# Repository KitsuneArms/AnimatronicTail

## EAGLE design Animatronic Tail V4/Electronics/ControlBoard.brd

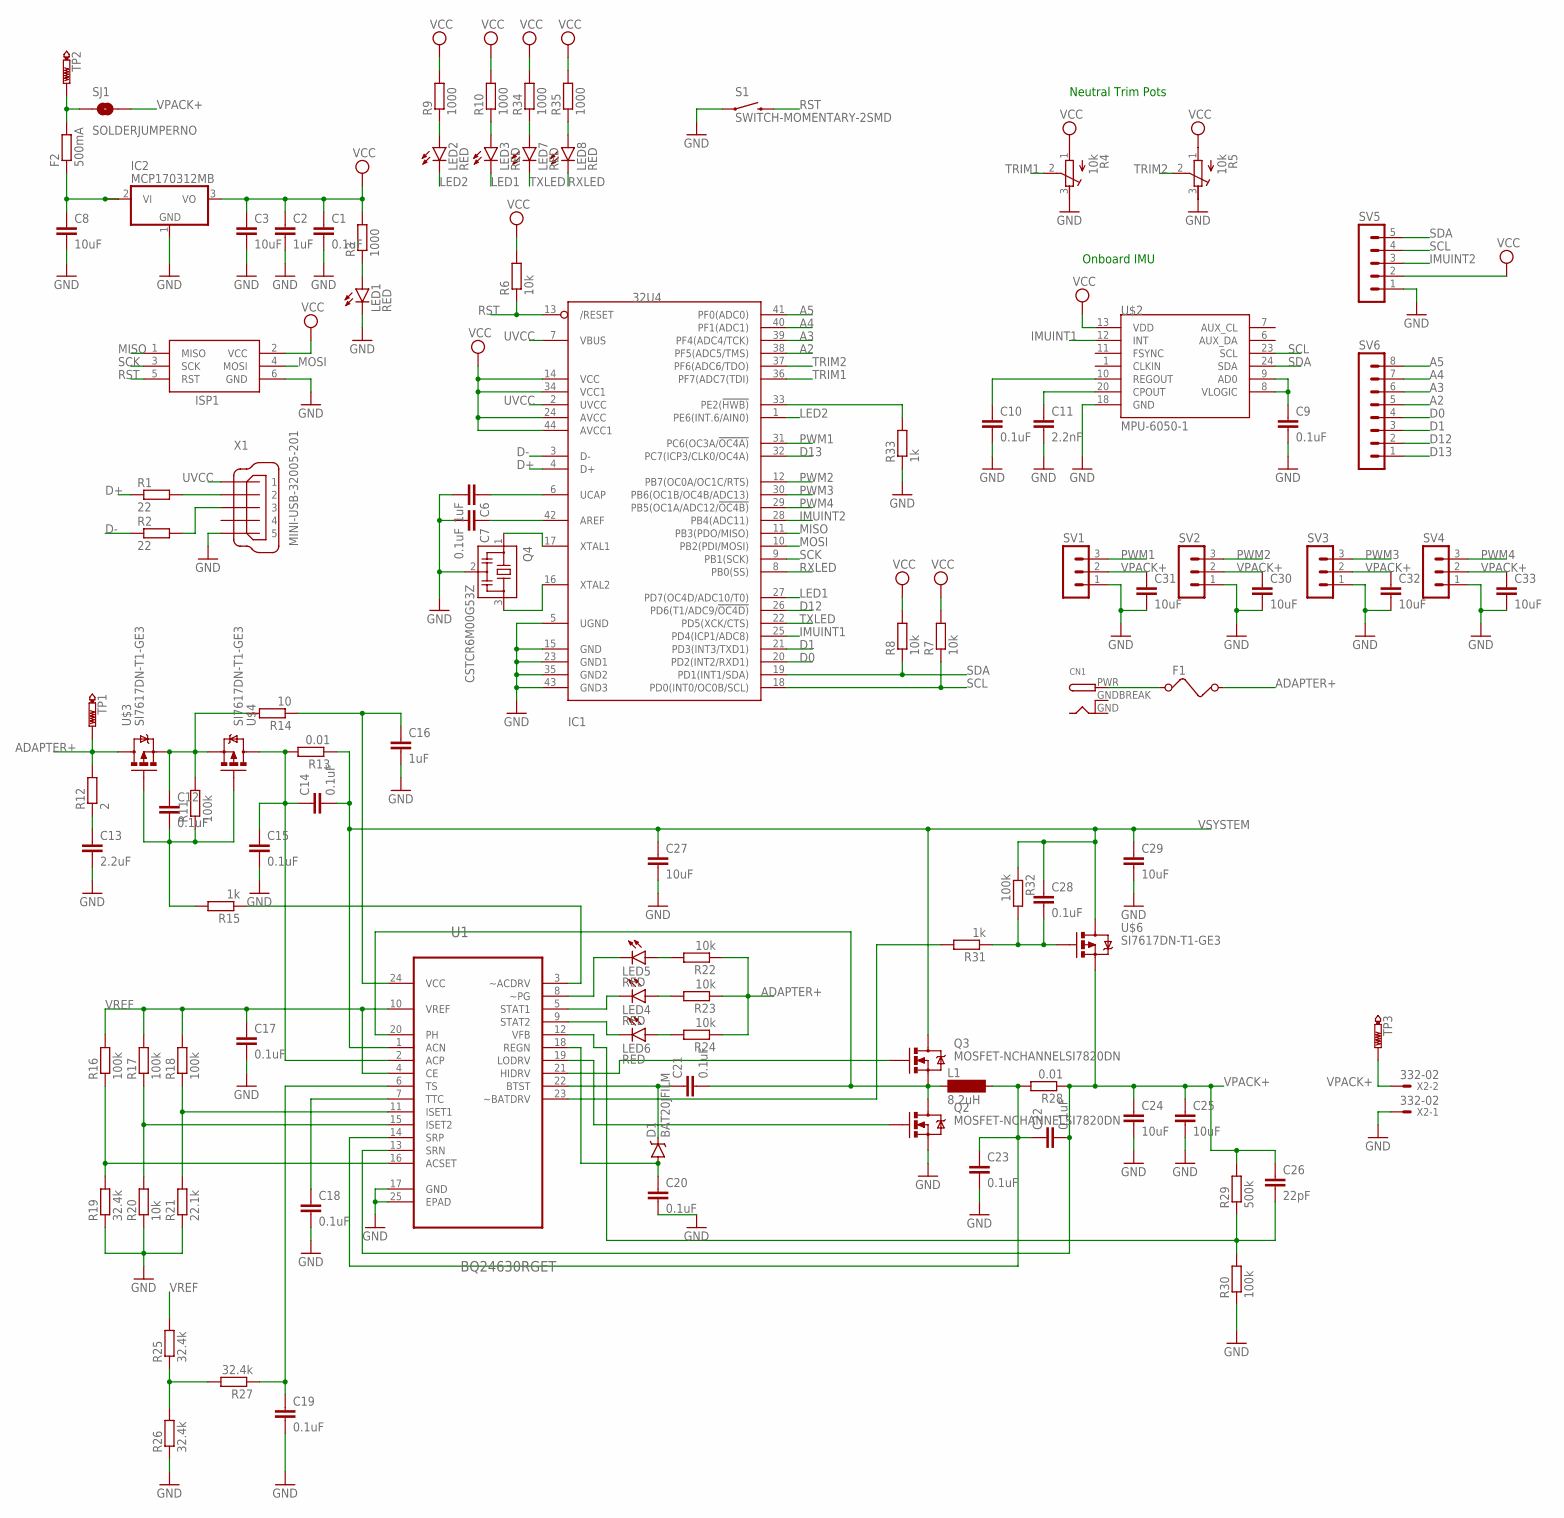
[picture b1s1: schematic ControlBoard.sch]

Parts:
C1, C7, C9, C10, C12, C14, C15, C17, C18, C19, C20, C21, C22, C23, C28: 0.1uF; C0603
C2, C6, C16: 1uF; C0603
C3, C8, C24, C25, C27, C29, C30, C31, C32, C33: 10uF; C0603
C11: 2.2nF; C0603
C13: 2.2uF; C0603
C26: 22pF; C0603
CN1: DCBARRELPTH; DCJACK_2MM_PTH
D1: BAT20JFILM; SOD-323
F1: FUSE
F2: 500mA; R0603
IC1: 32U4; TQFP44
IC2: MCP170312MB; SOT89
ISP1: AVRISP-6; AVRISP
L1: 8.2uH; SM-1206
LED1, LED2, LED3, LED4, LED5, LED6, LED7, LED8: RED; LED-1206
Q2, Q3: MOSFET-NCHANNELSI7820DN; POWERPAK1212-8
Q4: CSTCR6M00G53Z; CSTCR6M
R1, R2: 22; R0603
R3, R9, R10, R34, R35: 1000; R0603
R4, R5: 10k; RTRIM3299W
R6, R7, R8, R20, R22, R23, R24: 10k; R0603
R11, R16, R17, R18, R30, R32: 100k; R0603
R12: 2; R0603
R13, R28: 0.01; R0603
R14: 10; R0603
R15, R31, R33: 1k; R0603
R19, R25, R26, R27: 32.4k; R0603
R21: 22.1k; R0603
R29: 500k; R0603
S1: SWITCH-MOMENTARY-2SMD; TACTILE-SWITCH-SMD
SJ1: SOLDERJUMPERNO; SJ_2S-NO
SV1, SV2, SV3, SV4: MA03-1
SV5: MA05-1
SV6: MA08-1
TP1, TP2, TP3: PTR1PAD1-13; P1-13
U1: BQ24630RGET; QFN50P400X400X100-25N
U$2: MPU-6050-1; QFN-24-4MM2
U$3, U$4, U$6: SI7617DN-T1-GE3; POWERPAK1212-8
X1: MINI-USB-32005-201; 32005-201
X2: 332-02

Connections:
A2: IC1.38 (PF5(ADC5/TMS)), SV6.5
A3: IC1.39 (PF4(ADC4/TCK)), SV6.6
A4: IC1.40 (PF1(ADC1)), SV6.7
A5: IC1.41 (PF0(ADC0)), SV6.8
ADAPTER+: F1.2, R12.2, R22.1, R23.1, R24.1, TP1.TP, U$3.D1 (D), U$3.D2 (D), U$3.D3 (D), U$3.D4 (D), U$3.DPAD (D)
D0: IC1.20 (PD2(INT2/RXD1)), SV6.4
D1: IC1.21 (PD3(INT3/TXD1)), SV6.3
D12: IC1.26 (PD6(T1/ADC9/!OC4D)), SV6.2
D13: IC1.32 (PC7(ICP3/CLK0/OC4A)), SV6.1
D+: IC1.4 (D+), R1.1
D-: IC1.3 (D-), R2.1
GND: C1.2, C2.2, C3.2, C6.2, C7.2, C8.2, C9.2, C10.2, C11.2, C13.2, C15.2, C16.2, C17.2, C18.2, C19.2, C20.2, C23.2, C24.2, C25.2, C27.2, C29.2, C30.2, C31.2, C32.2, C33.2, CN1.GND, IC1.5 (UGND), IC1.15 (GND), IC1.23 (GND1), IC1.35 (GND2), IC1.43 (GND3), IC2.1 (GND), ISP1.6 (GND), LED1.C, Q2.S1 (S), Q2.S2 (S), Q2.S3 (S), Q4.2, R4.3 (E), R5.3 (E), R19.1, R20.1, R21.1, R26.1, R30.1, R33.1, S1.1, SV1.1, SV2.1, SV3.1, SV4.1, SV5.1, U1.17 (GND), U1.25 (EPAD), U$2.18 (GND), X1.5, X2.1
GNDBREAK: CN1.GNDBREAK
IMUINT1: IC1.25 (PD4(ICP1/ADC8)), U$2.12 (INT)
IMUINT2: IC1.28 (PB4(ADC11)), SV5.3
LED1: IC1.27 (PD7(OC4D/ADC10/T0)), LED3.C
LED2: IC1.1 (PE6(INT.6/AIN0)), LED2.C
MISO: IC1.11 (PB3(PDO/MISO)), ISP1.1 (MISO)
MOSI: IC1.10 (PB2(PDI/MOSI)), ISP1.4 (MOSI)
unnamed: IC1.16 (XTAL2), Q4.3
unnamed: IC1.17 (XTAL1), Q4.1
unnamed: R2.2, X1.3
unnamed: C6.1, IC1.6 (UCAP)
unnamed: C7.1, IC1.42 (AREF)
unnamed: C8.1, F2.1, IC2.2 (VI), IC2.2@1 (VI1)
unnamed: C9.1, U$2.8 (VLOGIC), U$2.9 (AD0)
unnamed: C11.1, U$2.20 (CPOUT)
unnamed: R1.2, X1.2
unnamed: C10.1, U$2.10 (REGOUT)
unnamed: LED1.A, R3.1
unnamed: LED3.A, R10.1
unnamed: LED2.A, R9.1
unnamed: C12.1, R11.2, R14.2, U$3.S1 (S), U$3.S2 (S), U$3.S3 (S), U$4.S1 (S), U$4.S2 (S), U$4.S3 (S)
unnamed: C12.2, R11.1, R15.2, U$3.G, U$4.G
unnamed: C13.1, R12.1
unnamed: C14.1, C15.1, R13.2, U1.2 (ACP), U$4.D1 (D), U$4.D2 (D), U$4.D3 (D), U$4.D4 (D), U$4.DPAD (D)
unnamed: R15.1, U1.3 (~ACDRV)
unnamed: C16.1, R14.1, U1.24 (VCC)
unnamed: R16.1, R19.2, U1.16 (ACSET)
unnamed: R17.1, R20.2, U1.15 (ISET2)
unnamed: R18.1, R21.2, U1.11 (ISET1)
unnamed: C18.1, U1.7 (TTC)
unnamed: C19.1, R27.1, U1.6 (TS)
unnamed: LED5.C, U1.8 (~PG)
unnamed: LED4.C, U1.5 (STAT1)
unnamed: LED6.C, U1.9 (STAT2)
unnamed: LED6.A, R24.2
unnamed: LED4.A, R23.2
unnamed: LED5.A, R22.2
unnamed: R25.1, R26.2, R27.2
unnamed: C21.1, D1.C, U1.22 (BTST)
unnamed: C20.1, D1.A, U1.18 (REGN)
unnamed: C21.2, L1.1, Q2.D1 (D), Q2.D2 (D), Q2.D3 (D), Q2.D4 (D), Q2.DPAD (D), Q3.S1 (S), Q3.S2 (S), Q3.S3 (S), U1.20 (PH)
unnamed: Q2.G, U1.19 (LODRV)
unnamed: Q3.G, U1.21 (HIDRV)
unnamed: C26.2, R29.1, R30.2, U1.12 (VFB)
unnamed: R31.2, U1.23 (~BATDRV)
unnamed: C28.2, R31.1, R32.2, U$6.G
unnamed: C22.1, C23.1, L1.2, R28.2, U1.14 (SRP)
unnamed: CN1.PWR, F1.1
unnamed: F2.2, SJ1.1, TP2.TP
unnamed: LED7.A, R34.1
unnamed: LED8.A, R35.1
unnamed: IC1.33 (PE2(!HWB)), R33.2
PWM1: IC1.31 (PC6(OC3A/!OC4A)), SV1.3
PWM2: IC1.12 (PB7(OC0A/OC1C/RTS)), SV2.3
PWM3: IC1.30 (PB6(OC1B/OC4B/ADC13)), SV3.3
PWM4: IC1.29 (PB5(OC1A/ADC12/!OC4B)), SV4.3
RST: IC1.13 (/RESET), ISP1.5 (RST), R6.1, S1.3 (2)
RXLED: IC1.8 (PB0(SS)), LED8.C
SCK: IC1.9 (PB1(SCK)), ISP1.3 (SCK)
SCL: IC1.18 (PD0(INT0/OC0B/SCL)), R7.1, SV5.4, U$2.23 (SCL)
SDA: IC1.19 (PD1(INT1/SDA)), R8.1, SV5.5, U$2.24 (SDA)
TRIM1: IC1.36 (PF7(ADC7(TDI)), R4.2 (S)
TRIM2: IC1.37 (PF6(ADC6/TDO)), R5.2 (S)
TXLED: IC1.22 (PD5(XCK/CTS)), LED7.C
UVCC: IC1.2 (UVCC), IC1.7 (VBUS), X1.1
VCC: C1.1, C2.1, C3.1, IC1.14 (VCC), IC1.24 (AVCC), IC1.34 (VCC1), IC1.44 (AVCC1), IC2.3 (VO), ISP1.2 (VCC), R3.2, R4.1 (A), R5.1 (A), R6.2, R7.2, R8.2, R9.2, R10.2, R34.2, R35.2, SV5.2, U$2.13 (VDD)
VPACK+: C22.2, C24.1, C25.1, C26.1, C30.1, C31.1, C32.1, C33.1, R28.1, R29.2, SJ1.2, SV1.2, SV2.2, SV3.2, SV4.2, TP3.TP, U1.13 (SRN), U$6.S1 (S), U$6.S2 (S), U$6.S3 (S), X2.2
VREF: C17.1, R16.2, R17.2, R18.2, R25.2, U1.4 (CE), U1.10 (VREF)
VSYSTEM: C14.2, C27.1, C28.1, C29.1, Q3.D1 (D), Q3.D2 (D), Q3.D3 (D), Q3.D4 (D), Q3.DPAD (D), R13.1, R32.1, U1.1 (ACN), U$6.D1 (D), U$6.D2 (D), U$6.D3 (D), U$6.D4 (D), U$6.DPAD (D)

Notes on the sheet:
Neutral Trim Pots
Onboard IMU

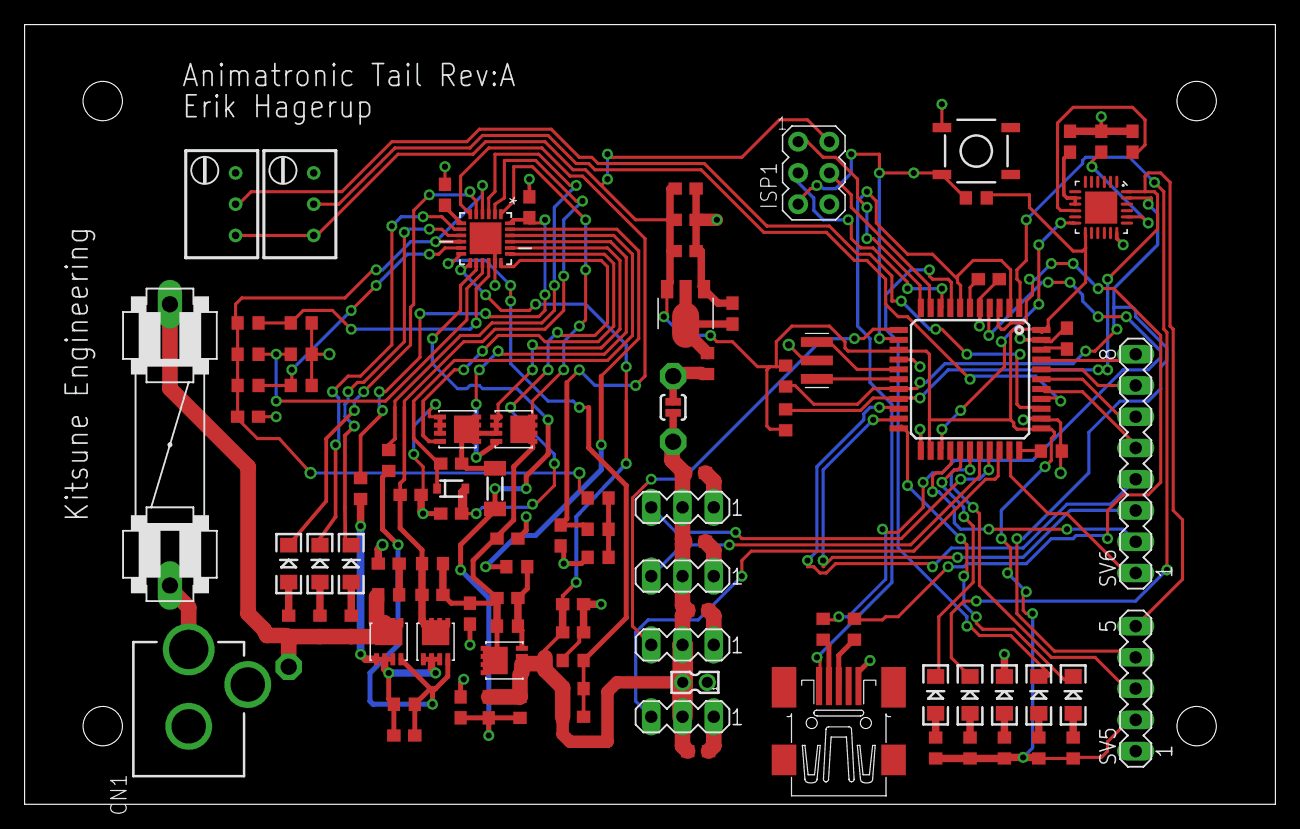
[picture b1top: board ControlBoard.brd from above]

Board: 2 copper layers, 101.7 x 63.4 mm, 103 parts (0 on the bottom side), 80 nets.

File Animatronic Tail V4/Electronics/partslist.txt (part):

Partlist

Exported from ControlBoard.brd at 9/28/2014 9:12:36 PM

EAGLE Version 7.0.0 Copyright (c) 1988-2014 CadSoft

Assembly variant: 

Part     Value                   Package               Library                                Position (inch)       Orientation

C1       0.1uF                   C0603                 eagle-ltspice                          (2.02 1.35)           R0
C2       1uF                     C0603                 eagle-ltspice                          (2.02 1.45)           R0
C3       10uF                    C0603                 eagle-ltspice                          (2.02 1.55)           R0
C4       22pf                    C0603                 eagle-ltspice                          (2.15 2.89)           R270
C5       22pf                    C0603                 eagle-ltspice                          (2.15 2.59)           R90
C6       1uF                     C0603                 eagle-ltspice                          (1.43 2.24)           R90
C7       0.1uF                   C0603                 eagle-ltspice                          (1.34 2.24)           R90
C8       10uF                    C0603                 eagle-ltspice                          (2.17 1.15)           R90
C9       0.1uF                   C0603                 eagle-ltspice                          (3.45 2.35)           R180
C10      0.1uF                   C0603                 eagle-ltspice                          (3.45 2.55)           R180
C11      2.2nF                   C0603                 eagle-ltspice                          (3.45 2.45)           R180
C12      0.1uF                   C0603                 eagle-ltspice                          (1.09 0.22)           R0
C13      2.2uF                   C0603                 eagle-ltspice                          (1.04 0.77)           R180
C14      0.1uF                   C0603                 eagle-ltspice                          (1.18 0.67)           R0
C15      0.1uF                   C0603                 eagle-ltspice                          (1.11 0.99)           R0
C16      1uF                     C0603                 eagle-ltspice                          (1.49 1.91)           R90
C17      0.1uF                   C0603                 eagle-ltspice                          (0.59 1.24)           R0
C18      0.1uF                   C0603                 eagle-ltspice                          (1.22 1.95)           R90
C19      0.1uF                   C0603                 eagle-ltspice                          (1.59 0.86)           R270
C20      0.1uF                   C0603                 eagle-ltspice                          (1.24 0.93)           R180
C21      0.1uF                   C0603                 eagle-ltspice                          (1.24 1.09)           R0
C22      0.1uF                   C0603                 eagle-ltspice                          (1.36 0.31)           R90
C23      0.1uF                   C0603                 eagle-ltspice                          (1.27 0.31)           R90
C24      10uF                    C0603                 eagle-ltspice                          (1.63 0.64)           R0
C25      10uF                    C0603                 eagle-ltspice                          (1.63 0.55)           R0
C26      22pF                    C0603                 eagle-ltspice                          (1.63 0.28)           R0
C27      10uF                    C0603                 eagle-ltspice                          (1.42 0.85)           R0
C28      0.1uF                   C0603                 eagle-ltspice                          (1.42 0.66)           R0
C29      10uF                    C0603                 eagle-ltspice                          (1.3 0.61)            R270
C30      10uF                    C0603                 eagle-ltspice                          (2.01 0.62)           R0
C31      10uF                    C0603                 eagle-ltspice                          (2.01 0.17)           R0
CN1                              DCJACK_2MM_PTH        adafruit                               (0.34 -0.04)          R0
D1       BAT20JFILM              SOD-323               SparkFun-DiscreteSemi                  (1.24 1.01)           R0
F1                               FUSE                  special                                (0.28 1.14)           R90
F2       500mA                   R0603                 eagle-ltspice                          (2.09 0.99)           R270
IC1      32U4                    TQFP44                adafruit                               (1.58 2.84)           R0
IC2      MCP170312MB             SOT89                 linear                                 (2.02 1.15)           R180
ISP1     AVRISP-6                AVRISP                adafruit                               (0.88 2.25)           R0
L1       8.2uH                   SM-1206               inductor-neosid                        (1.38 1.01)           R270
LED1     RED                     LED-1206              SparkFun-LED                           (3.09 0.36)           R90
LED2     RED                     LED-1206              SparkFun-LED                           (2.98 0.36)           R90
LED3     RED                     LED-1206              SparkFun-LED                           (2.87 0.36)           R90
LED4     RED                     LED-1206              SparkFun-LED                           (0.72 0.77)           R90
LED5     RED                     LED-1206              SparkFun-LED                           (0.82 0.77)           R90
LED6     RED                     LED-1206              SparkFun-LED                           (0.92 0.77)           R90
Q1       8Mhz                    HC49UP                crystal                                (1.98 2.74)           R270
Q2       MOSFET-NCHANNELSI7820DN POWERPAK1212-8        SparkFun-DiscreteSemi                  (1.26 1.2)            R0
Q3       MOSFET-NCHANNELSI7820DN POWERPAK1212-8        SparkFun-DiscreteSemi                  (1.44 1.2)            R0
R1       22                      R0603                 eagle-ltspice                          (2.43 0.56)           R270
R2       22                      R0603                 eagle-ltspice                          (2.53 0.56)           R270
R3       1000                    R0603                 eagle-ltspice                          (3.09 0.19)           R270
R4       10k                     RTRIM3299W            rcl                                    (0.23 2.6)            R0
R5       10k                     RTRIM3299W            rcl                                    (0.48 2.6)            R0
R6       10k                     R0603                 eagle-ltspice                          (2.63 2.62)           R180
R7       10k                     R0603                 eagle-ltspice                          (2.63 2.82)           R180
R8       10k                     R0603                 eagle-ltspice                          (2.63 2.72)           R180
R9       1000                    R0603                 eagle-ltspice                          (2.98 0.19)           R270
R10      1000                    R0603                 eagle-ltspice                          (2.87 0.19)           R270
R11      100k                    R0603                 eagle-ltspice                          (1.09 0.32)           R180
R12      2                       R0603                 eagle-ltspice                          (1.04 0.67)           R180
R13      0.01                    R0603                 eagle-ltspice                          (1.18 0.77)           R180
R14      10                      R0603                 eagle-ltspice                          (0.95 1.01)           R270
R15      1k                      R0603                 eagle-ltspice                          (1.04 1.1)            R270
R16      100k                    R0603                 eagle-ltspice                          (0.59 1.54)           R180
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
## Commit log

2014-10-05 Initial Upload
2014-10-05 Clean up

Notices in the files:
parts and their libraries:
SparkFun-Electromechanical: Licensing: Creative Commons ShareAlike 4.0 International - https://creativecommons.org/licenses/by-sa/4.0
